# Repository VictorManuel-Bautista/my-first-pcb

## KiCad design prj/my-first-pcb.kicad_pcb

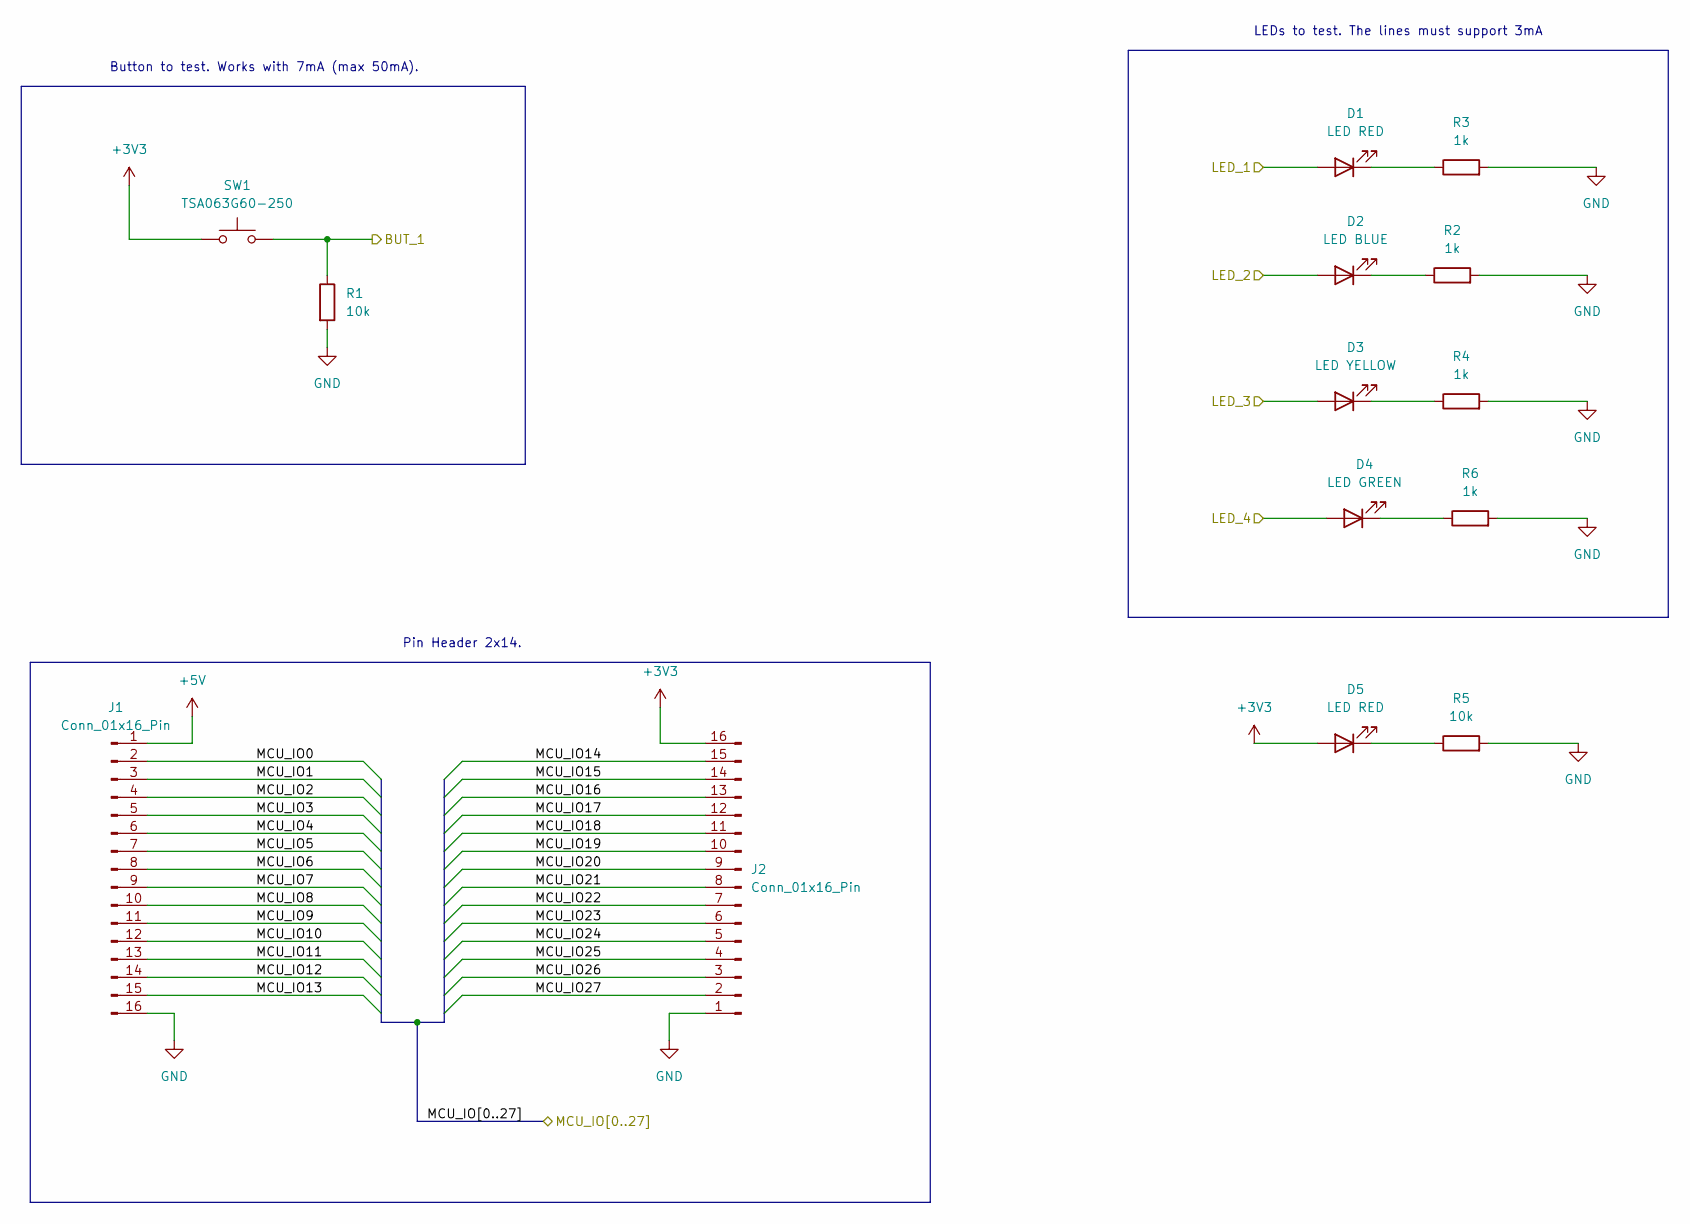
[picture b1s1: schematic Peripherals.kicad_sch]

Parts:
D1, D5: LED RED; LED_0603_1608Metric; LCSC C2286
D2: LED BLUE; LED_0603_1608Metric; LCSC C2288
D3: LED YELLOW; LED_0603_1608Metric; LCSC C2290
D4: LED GREEN; LED_0603_1608Metric; LCSC C2289
J1, J2: Conn_01x16_Pin; PinHeader_1x16_P2.54mm_Vertical
R1, R5: 10k; R_0603_1608Metric; LCSC C25804
R2, R3, R4, R6: 1k; R_0603_1608Metric; LCSC C21190
SW1: TSA063G60-250; SW_SPST_Omron_B3FS-105xP; LCSC C294566

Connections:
+3V3: D5.2 (A), J2.16, SW1.1; also elsewhere on the board
+5V: J1.1; also elsewhere on the board
/MCU/MCU_IO0: J1.2; also elsewhere on the board
/MCU/MCU_IO1: J1.3; also elsewhere on the board
/MCU/MCU_IO2: J1.4; also elsewhere on the board
/MCU/MCU_IO3: J1.5; also elsewhere on the board
/MCU/MCU_IO4: J1.6; also elsewhere on the board
/MCU/MCU_IO5: J1.7; also elsewhere on the board
/MCU/MCU_IO6: J1.8; also elsewhere on the board
/MCU/MCU_IO7: J1.9; also elsewhere on the board
/MCU/MCU_IO8: J1.10; also elsewhere on the board
/MCU/MCU_IO9: J1.11; also elsewhere on the board
/MCU/MCU_IO10: J1.12; also elsewhere on the board
/MCU/MCU_IO11: J1.13; also elsewhere on the board
/MCU/MCU_IO12: J1.14; also elsewhere on the board
/MCU/MCU_IO13: J1.15; also elsewhere on the board
/MCU/MCU_IO14: J2.15; also elsewhere on the board
/MCU/MCU_IO15: J2.14; also elsewhere on the board
/MCU/MCU_IO16: J2.13; also elsewhere on the board
/MCU/MCU_IO17: J2.12; also elsewhere on the board
/MCU/MCU_IO18: J2.11, R1.1, SW1.2; also elsewhere on the board
/MCU/MCU_IO19: D4.2 (A), J2.10; also elsewhere on the board
/MCU/MCU_IO20: D3.2 (A), J2.9; also elsewhere on the board
/MCU/MCU_IO21: D2.2 (A), J2.8; also elsewhere on the board
/MCU/MCU_IO22: D1.2 (A), J2.7; also elsewhere on the board
/MCU/MCU_IO23: J2.6; also elsewhere on the board
/MCU/MCU_IO24: J2.5; also elsewhere on the board
/MCU/MCU_IO25: J2.4; also elsewhere on the board
/MCU/MCU_IO26: J2.3; also elsewhere on the board
/MCU/MCU_IO27: J2.2; also elsewhere on the board
GND: J1.16, J2.1, R1.2, R2.2, R3.2, R4.2, R5.2, R6.2; also elsewhere on the board
unnamed: D1.1 (K), R3.1
unnamed: D2.1 (K), R2.1
unnamed: D3.1 (K), R4.1
unnamed: D4.1 (K), R6.1
unnamed: D5.1 (K), R5.1

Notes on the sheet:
Button to test. Works with 7mA (max 50mA).
LEDs to test. The lines must support 3mA
Pin Header 2x14.

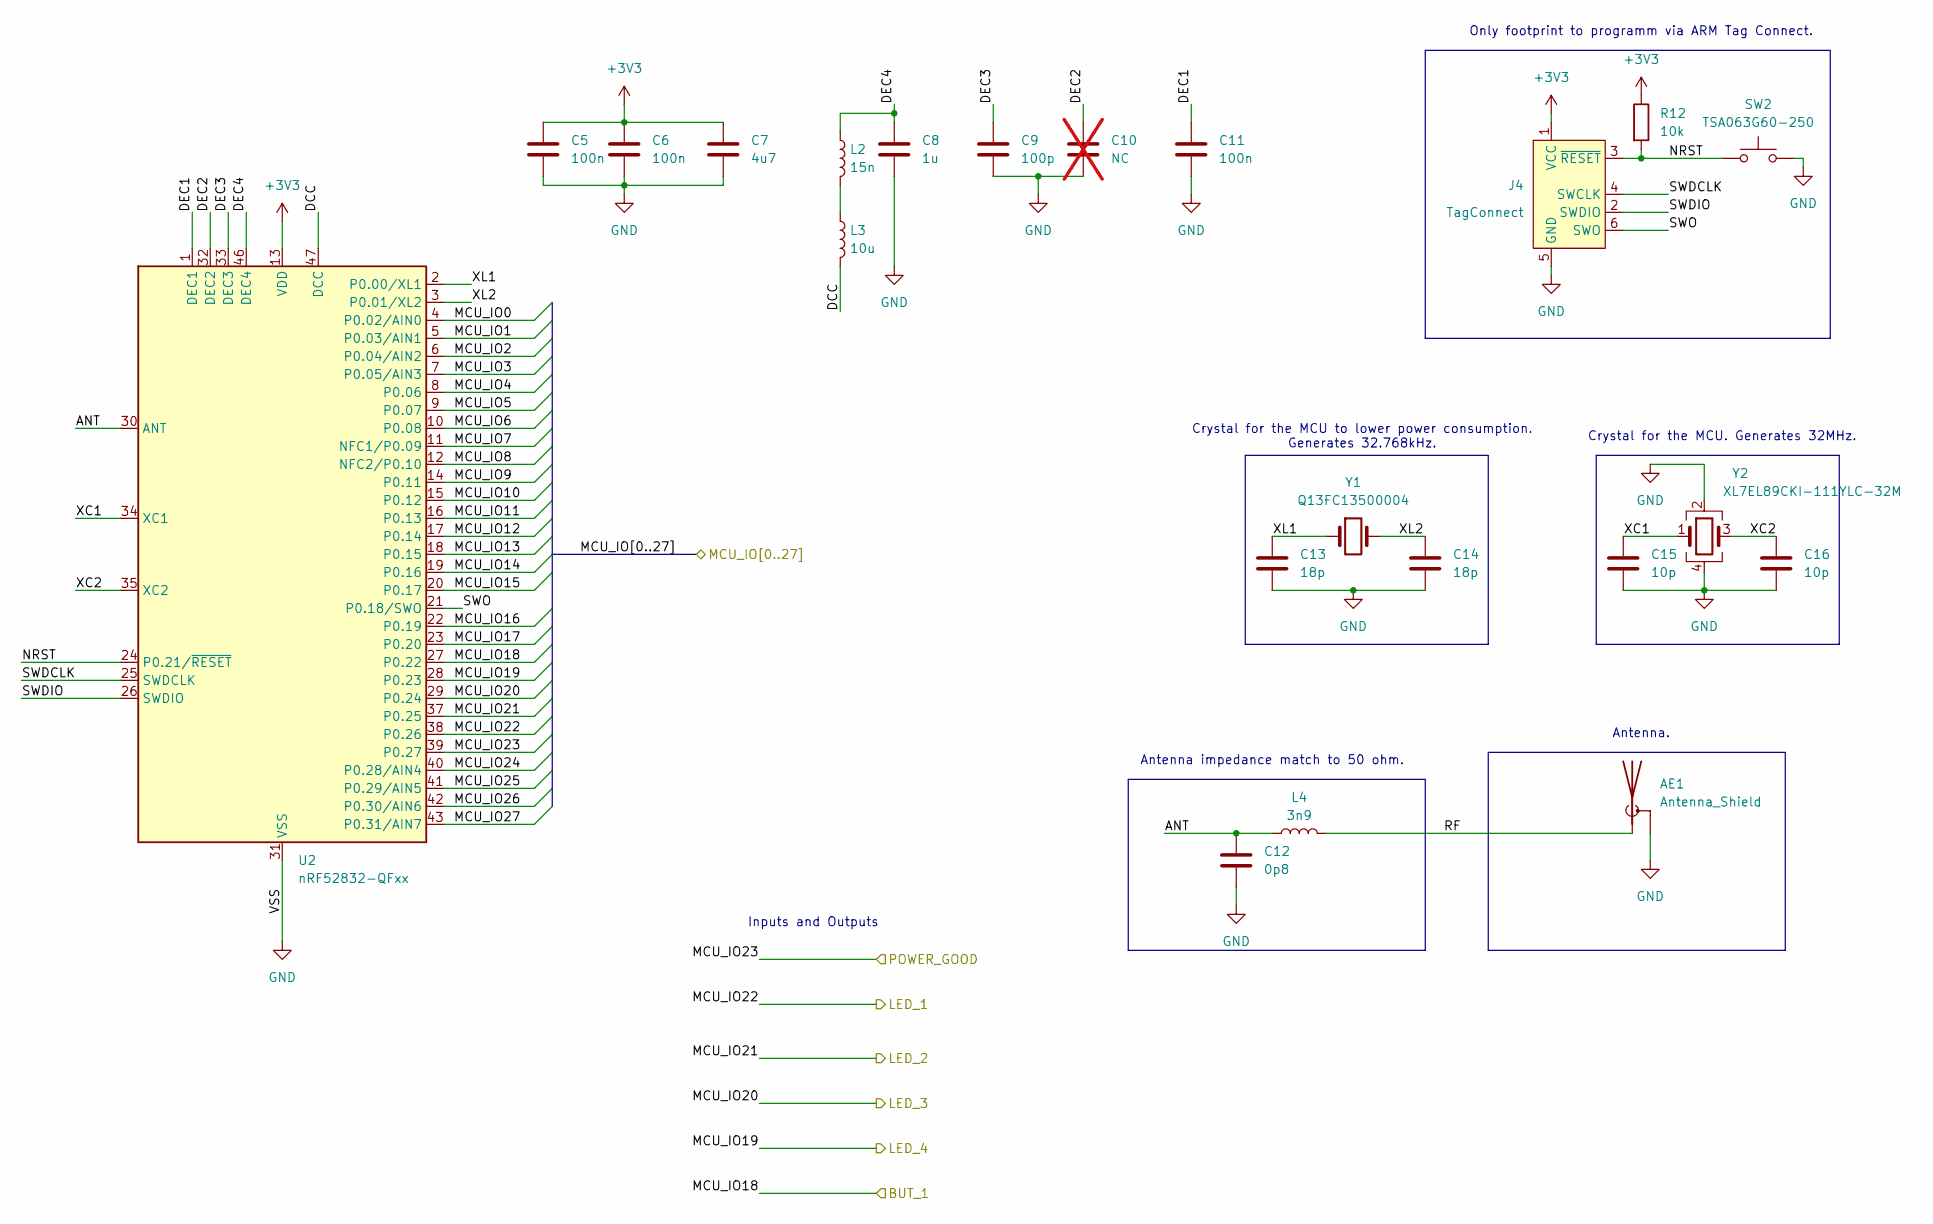
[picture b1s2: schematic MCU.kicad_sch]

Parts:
AE1: Antenna_Shield; Texas_SWRA117D_2.4GHz_Left
C5, C6, C11: 100n; C_0603_1608Metric; LCSC C14663
C7: 4u7; C_0603_1608Metric; LCSC C1705
C8: 1u; C_0603_1608Metric; LCSC C1592
C9: 100p; C_0603_1608Metric; LCSC C14858
C10: NC; C_0603_1608Metric; not fitted
C12: 0p8; C_0402_1005Metric; LCSC C40459
C13, C14: 18p; C_0603_1608Metric; LCSC C1647
C15, C16: 10p; C_0603_1608Metric; LCSC C1634
J4: TagConnect; Tag-Connect_TC2030-IDC-FP_2x03_P1.27mm_Vertical
L2: 15n; L_0603_1608Metric; LCSC C304267
L3: 10u; L_0805_2012Metric; LCSC C18221303
L4: 3n9; L_0402_1005Metric; LCSC C14033
R12: 10k; R_0603_1608Metric; LCSC C25804
SW2: TSA063G60-250; SW_SPST_Omron_B3FS-105xP; LCSC C294566
U2: nRF52832-QFxx; QFN-48-1EP_6x6mm_P0.4mm_EP4.6x4.6mm; LCSC C77540
Y1: Q13FC13500004; Crystal_SMD_3215-2Pin_3.2x1.5mm; LCSC C32346
Y2: XL7EL89CKI-111YLC-32M; Crystal_SMD_2016-4Pin_2.0x1.6mm; LCSC C2965582

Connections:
+3V3: C5.1, C6.1, C7.1, J4.1 (VCC), R12.1, U2.13 (VDD), U2.36 (VDD), U2.48 (VDD); also elsewhere on the board
/MCU/ANT: C12.1, L4.1, U2.30 (ANT)
/MCU/DCC: L3.2, U2.47 (DCC)
/MCU/DEC1: C11.1, U2.1 (DEC1)
/MCU/DEC2: C10.1, U2.32 (DEC2)
/MCU/DEC3: C9.1, U2.33 (DEC3)
/MCU/DEC4: C8.1, L2.1, U2.46 (DEC4)
/MCU/MCU_IO0: U2.4 (P0.02/AIN0); also elsewhere on the board
/MCU/MCU_IO1: U2.5 (P0.03/AIN1); also elsewhere on the board
/MCU/MCU_IO2: U2.6 (P0.04/AIN2); also elsewhere on the board
/MCU/MCU_IO3: U2.7 (P0.05/AIN3); also elsewhere on the board
/MCU/MCU_IO4: U2.8 (P0.06); also elsewhere on the board
/MCU/MCU_IO5: U2.9 (P0.07); also elsewhere on the board
/MCU/MCU_IO6: U2.10 (P0.08); also elsewhere on the board
/MCU/MCU_IO7: U2.11 (NFC1/P0.09); also elsewhere on the board
/MCU/MCU_IO8: U2.12 (NFC2/P0.10); also elsewhere on the board
/MCU/MCU_IO9: U2.14 (P0.11); also elsewhere on the board
/MCU/MCU_IO10: U2.15 (P0.12); also elsewhere on the board
/MCU/MCU_IO11: U2.16 (P0.13); also elsewhere on the board
/MCU/MCU_IO12: U2.17 (P0.14); also elsewhere on the board
/MCU/MCU_IO13: U2.18 (P0.15); also elsewhere on the board
/MCU/MCU_IO14: U2.19 (P0.16); also elsewhere on the board
/MCU/MCU_IO15: U2.20 (P0.17); also elsewhere on the board
/MCU/MCU_IO16: U2.22 (P0.19); also elsewhere on the board
/MCU/MCU_IO17: U2.23 (P0.20); also elsewhere on the board
/MCU/MCU_IO18: U2.27 (P0.22); also elsewhere on the board
/MCU/MCU_IO19: U2.28 (P0.23); also elsewhere on the board
/MCU/MCU_IO20: U2.29 (P0.24); also elsewhere on the board
/MCU/MCU_IO21: U2.37 (P0.25); also elsewhere on the board
/MCU/MCU_IO22: U2.38 (P0.26); also elsewhere on the board
/MCU/MCU_IO23: U2.39 (P0.27); also elsewhere on the board
/MCU/MCU_IO24: U2.40 (P0.28/AIN4); also elsewhere on the board
/MCU/MCU_IO25: U2.41 (P0.29/AIN5); also elsewhere on the board
/MCU/MCU_IO26: U2.42 (P0.30/AIN6); also elsewhere on the board
/MCU/MCU_IO27: U2.43 (P0.31/AIN7); also elsewhere on the board
/MCU/NRST: J4.3 (~RESET), R12.2, SW2.1, U2.24 (P0.21/~RESET)
/MCU/RF: AE1.1 (A), L4.2
/MCU/SWDCLK: J4.4 (SWCLK), U2.25 (SWDCLK)
/MCU/SWDIO: J4.2 (SWDIO), U2.26 (SWDIO)
/MCU/SWO: J4.6 (SWO), U2.21 (P0.18/SWO)
/MCU/XC1: C15.1, U2.34 (XC1), Y2.1
/MCU/XC2: C16.1, U2.35 (XC2), Y2.3
/MCU/XL1: C13.1, U2.2 (P0.00/XL1), Y1.1
/MCU/XL2: C14.1, U2.3 (P0.01/XL2), Y1.2
GND: AE1.2 (Shield), C5.2, C6.2, C7.2, C8.2, C9.2, C10.2, C11.2, C12.2, C13.2, C14.2, C15.2, C16.2, J4.5 (GND), SW2.2, U2.31 (VSS), U2.45 (VSS), U2.49 (VSS), Y2.2, Y2.4; also elsewhere on the board
unnamed: L2.2, L3.1

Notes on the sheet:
Antenna impedance match to 50 ohm.
Antenna.
Crystal for the MCU. Generates 32MHz.
Inputs and Outputs
Crystal for the MCU to lower power consumption. Generates 32.768kHz.
Only footprint to programm via ARM Tag Connect.

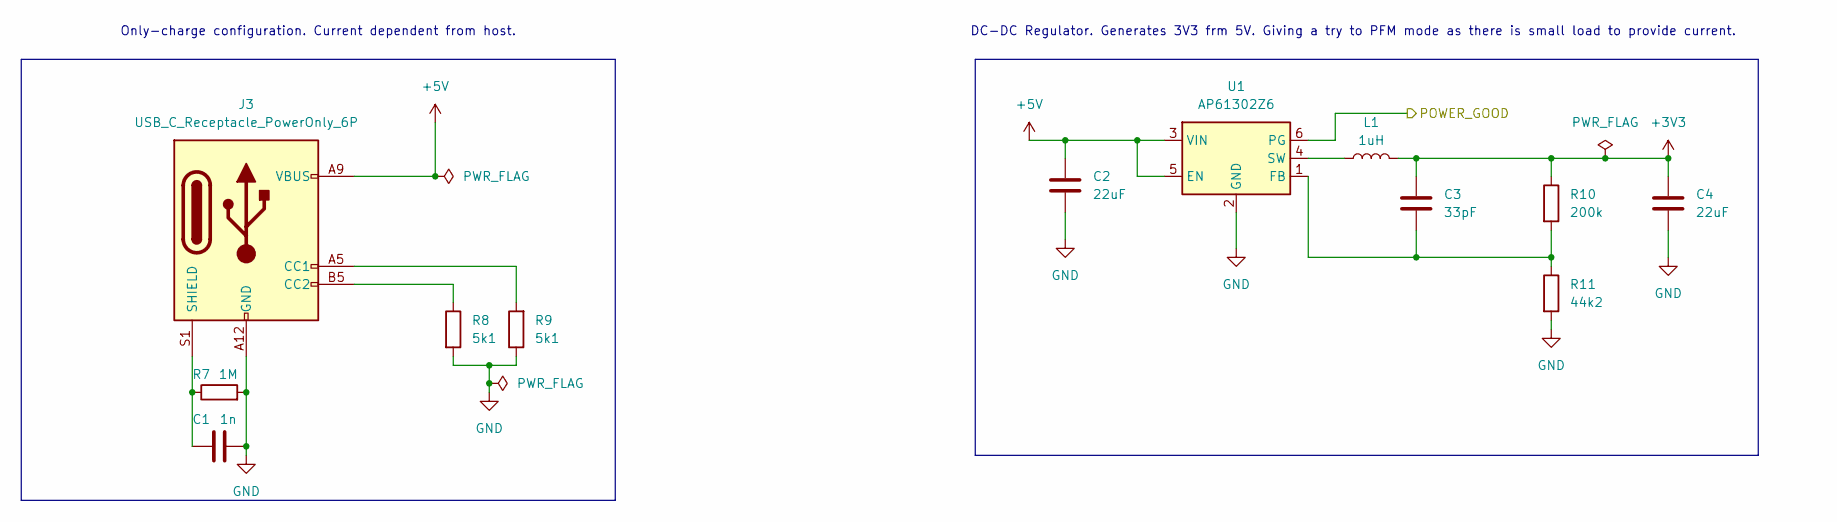
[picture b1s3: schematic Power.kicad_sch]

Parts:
C1: 1n; C_0603_1608Metric; LCSC C1588
C2, C4: 22uF; C_0603_1608Metric; LCSC C59461
C3: 33pF; C_0603_1608Metric; LCSC C1663
J3: USB_C_Receptacle_PowerOnly_6P; USB_C_Receptacle_GCT_USB4125-xx-x-0190_6P_TopMnt_Horizontal; LCSC C456012
L1: 1uH; L_Changjiang_FTC201610S; LCSC C2981230
R7: 1M; R_0603_1608Metric; LCSC C22935
R8, R9: 5k1; R_0603_1608Metric; LCSC C23186
R10: 200k; R_0603_1608Metric; LCSC C25811
R11: 44k2; R_0603_1608Metric; LCSC C23056
U1: AP61302Z6; SOT-563; LCSC C3193204

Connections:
+3V3: C3.1, C4.1, L1.2, R10.1; also elsewhere on the board
+5V: C2.1, J3.A9 (VBUS), J3.B9 (VBUS), U1.3 (VIN), U1.5 (EN); also elsewhere on the board
/MCU/MCU_IO23: U1.6 (PG); also elsewhere on the board
GND: C1.2, C2.2, C4.2, J3.A12 (GND), J3.B12 (GND), R7.2, R8.2, R9.1, R11.2, U1.2 (GND); also elsewhere on the board
unnamed: J3.A5 (CC1), R9.2
unnamed: J3.B5 (CC2), R8.1
unnamed: C1.1, J3.S1 (SHIELD), R7.1
unnamed: C3.2, R10.2, R11.1, U1.1 (FB)
unnamed: L1.1, U1.4 (SW)

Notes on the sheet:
Only-charge configuration. Current dependent from host.
DC-DC Regulator. Generates 3V3 frm 5V. Giving a try to PFM mode as there is small load to provide current.

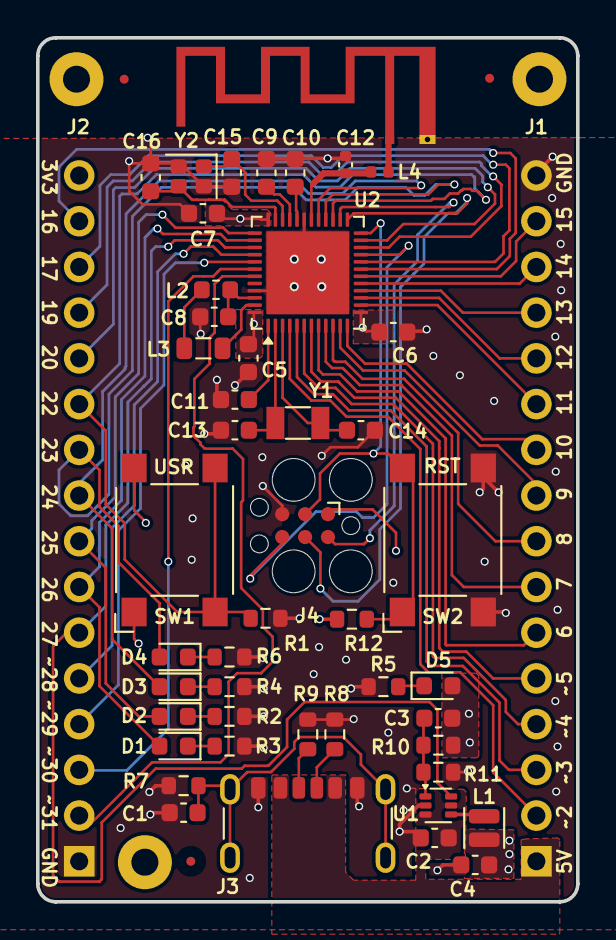
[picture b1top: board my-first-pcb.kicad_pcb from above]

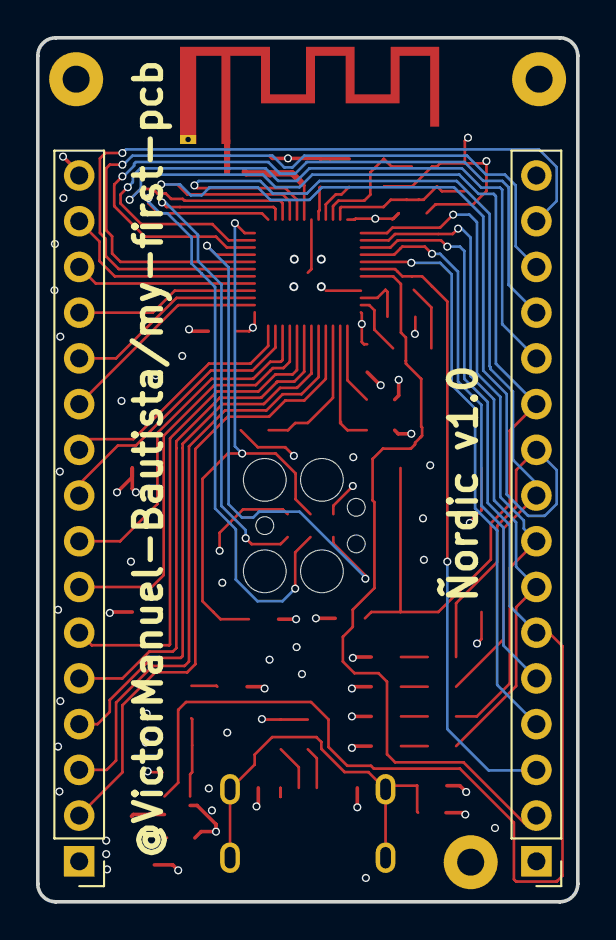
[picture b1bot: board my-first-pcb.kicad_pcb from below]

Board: 4 copper layers, 30.0 x 48.0 mm, 48 parts (2 on the bottom side), 57 nets.

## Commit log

2025-12-29 pcb routing finished
2026-01-29 PCB routed trial 2
2026-02-03 v1 ready
